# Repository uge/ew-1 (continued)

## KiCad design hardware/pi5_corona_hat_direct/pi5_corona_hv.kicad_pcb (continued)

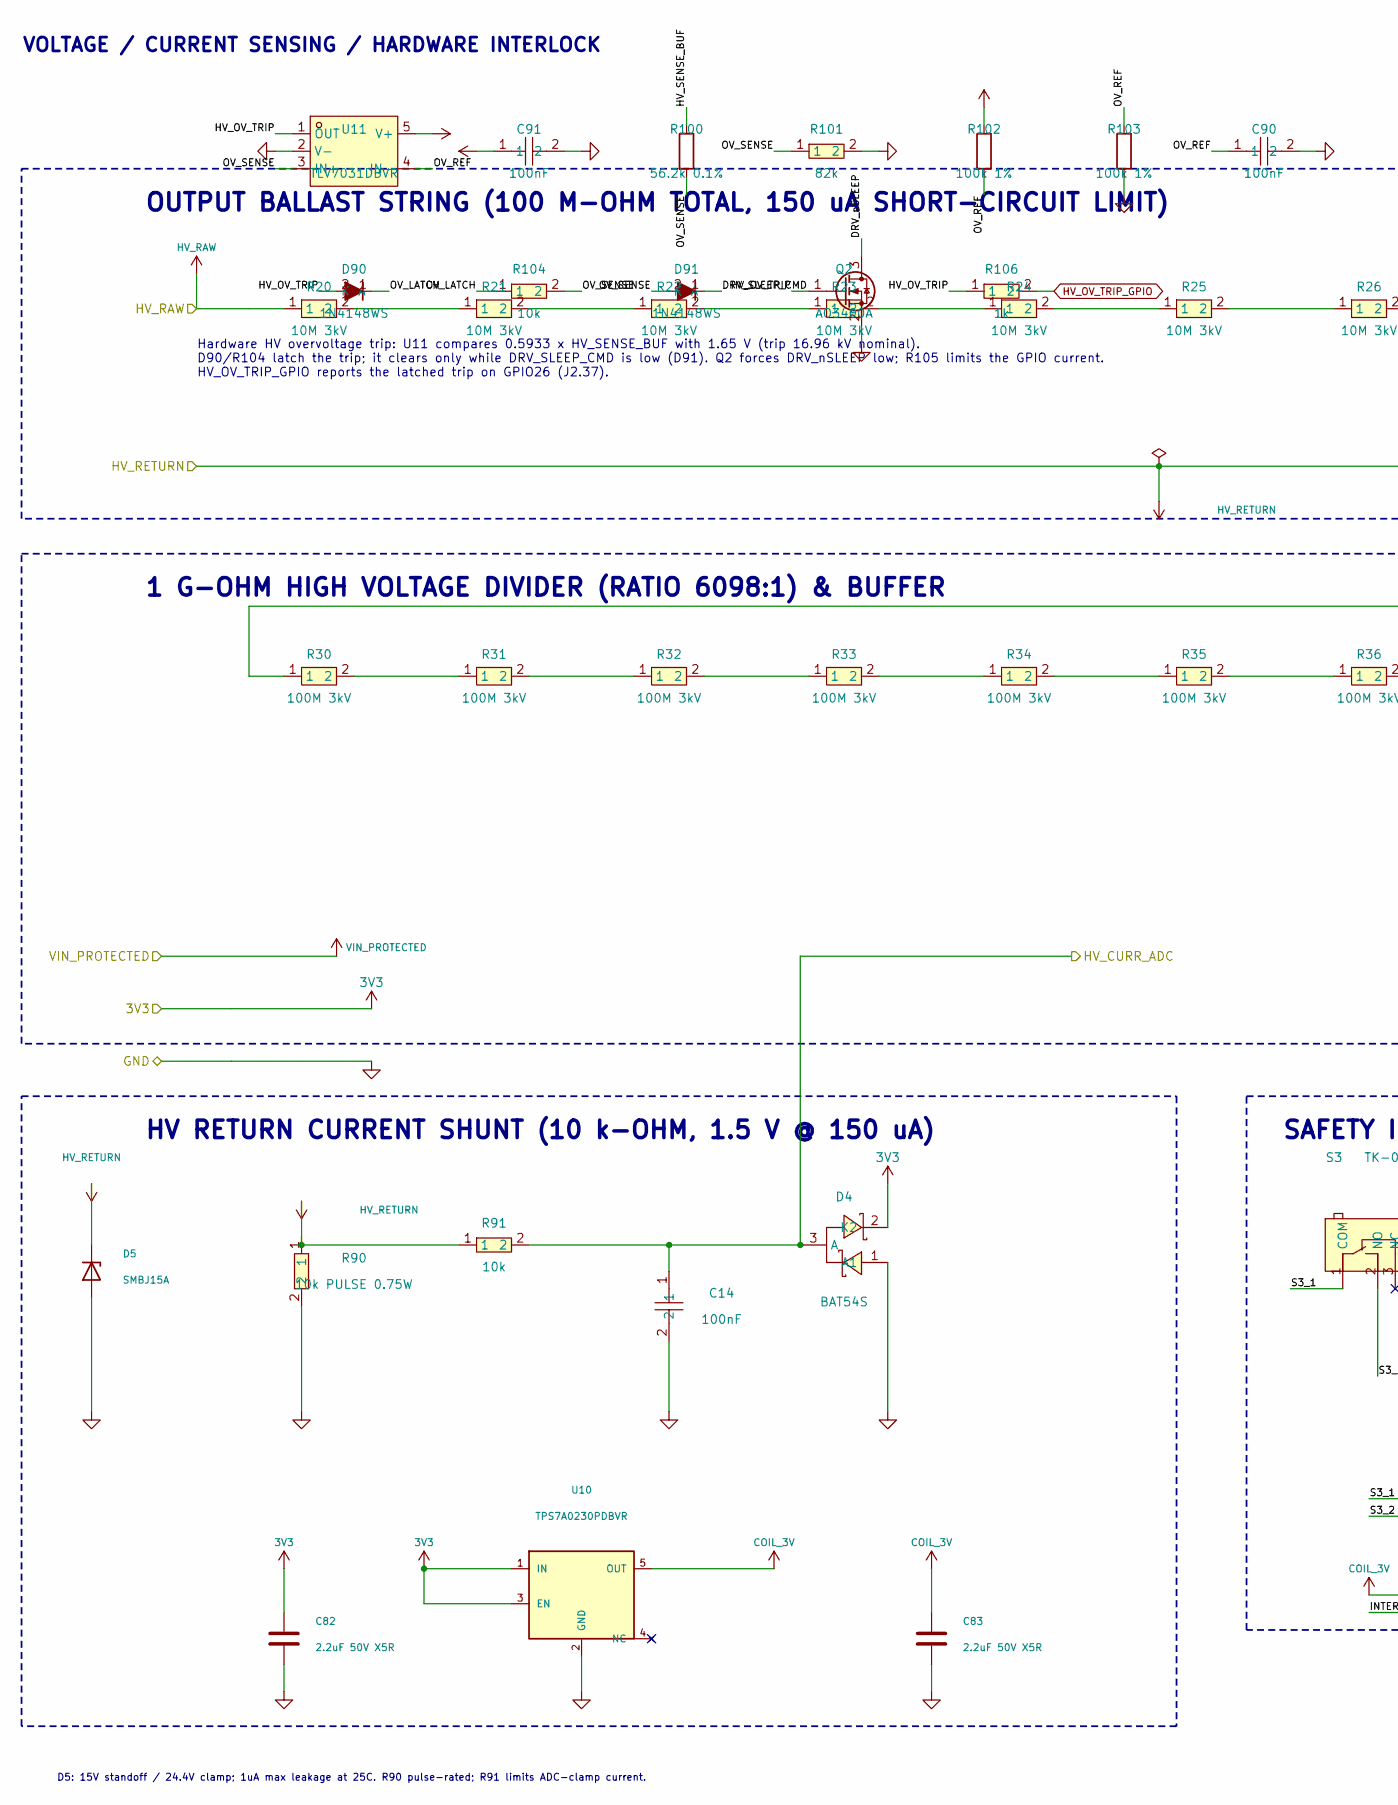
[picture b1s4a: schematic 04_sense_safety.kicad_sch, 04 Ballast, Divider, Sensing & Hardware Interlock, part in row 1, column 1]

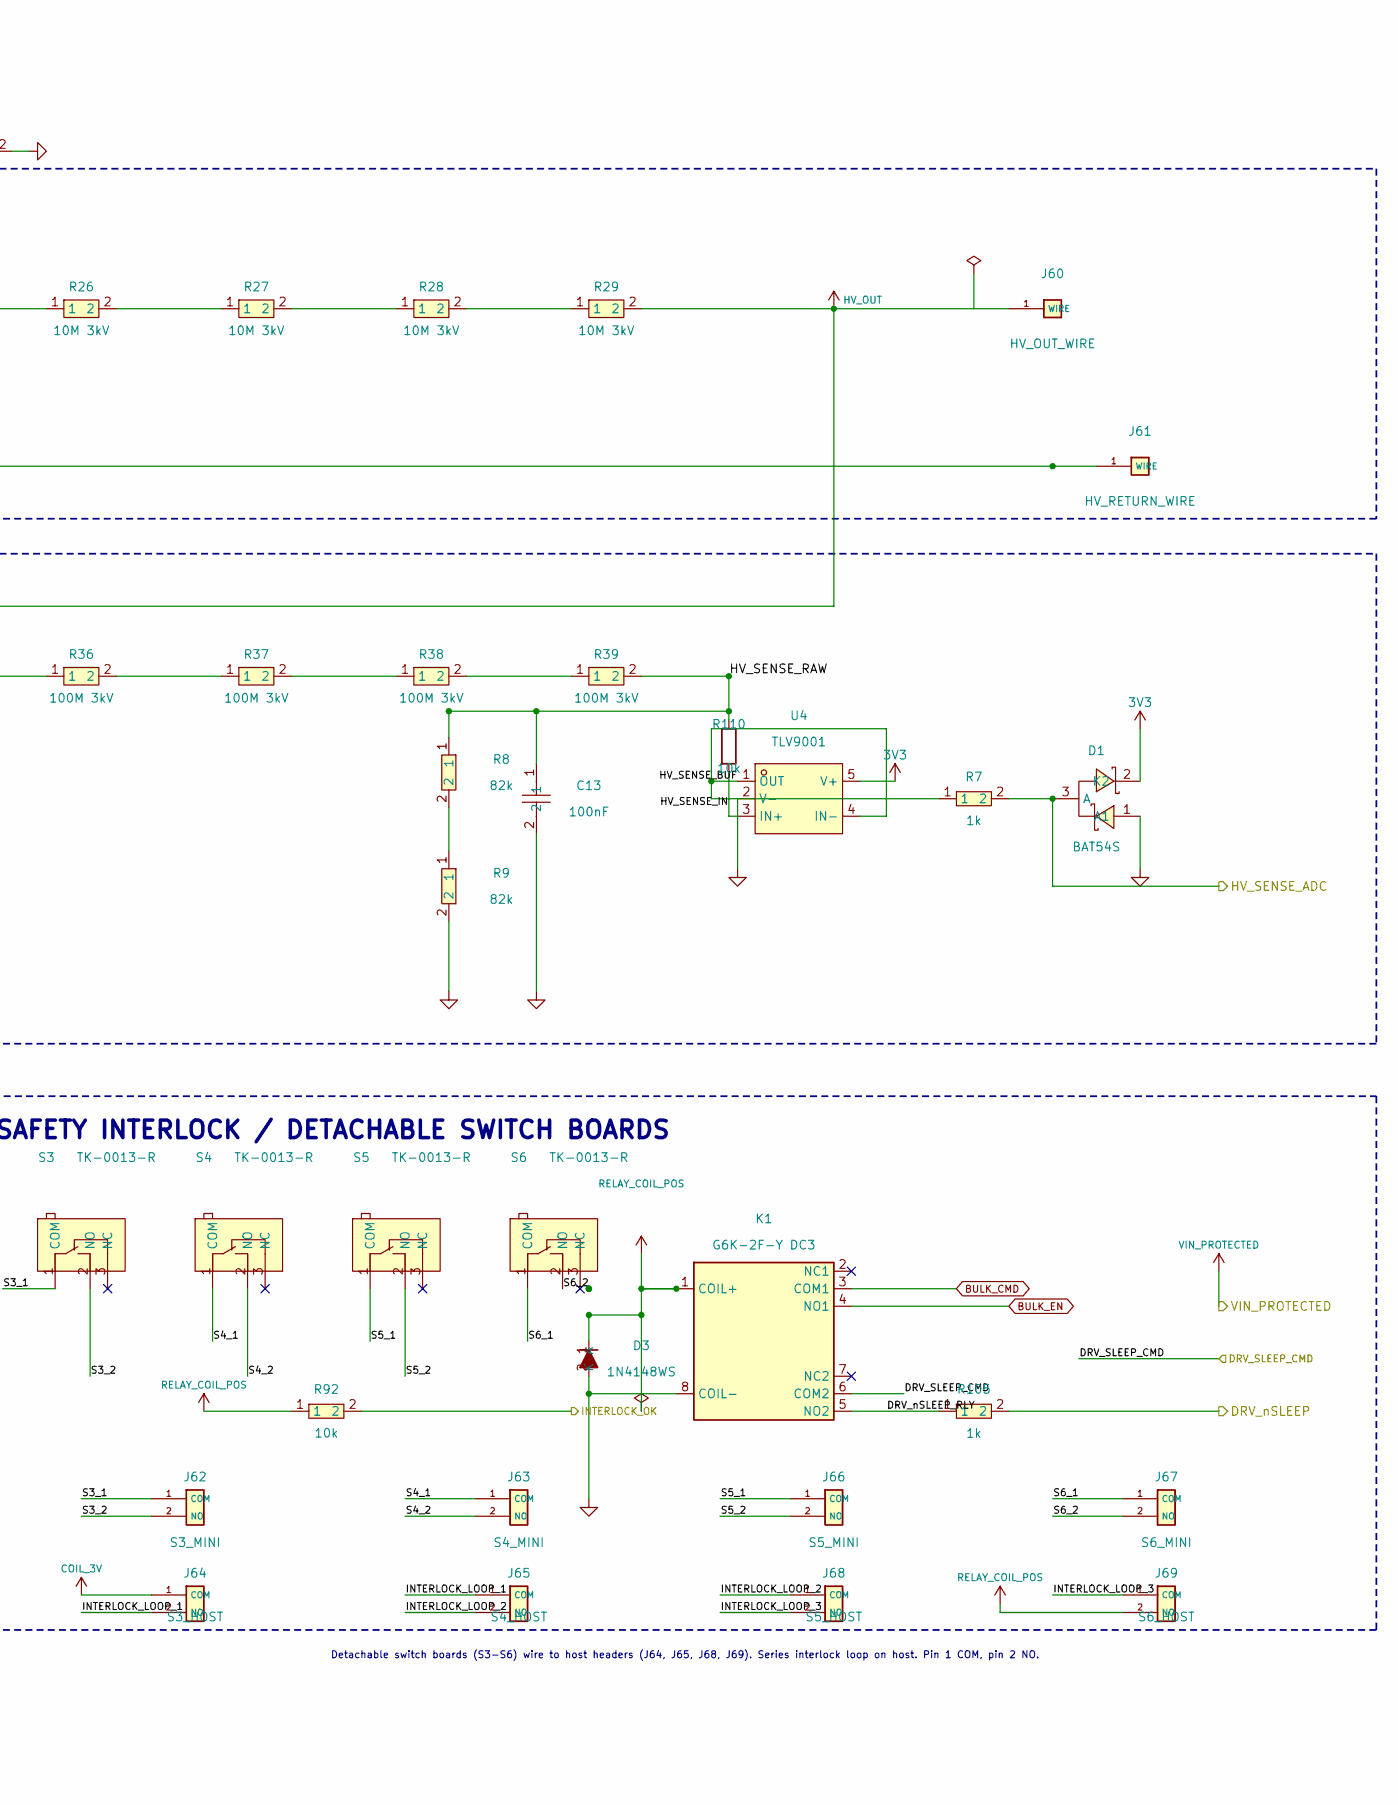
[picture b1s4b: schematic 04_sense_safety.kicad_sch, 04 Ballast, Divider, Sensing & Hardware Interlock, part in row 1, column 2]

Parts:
C13, C14, C90, C91: 100nF; C0603; MPN CC0603KRX7R9BB104; LCSC Part C14663
C82, C83: 2.2uF 50V X5R; C_0805_2012Metric; MPN CL21A225KBQNNNE; LCSC C377773
D1, D4: BAT54S; SOT-23-3_L2.9-W1.3-P1.90-LS2.4-BR; MPN BAT54S; LCSC Part C83935
D3, D90, D91: 1N4148WS; D_SOD-323; MPN 1N4148WS; LCSC Part C2128
D5: SMBJ15A; D_SMB; MPN SMBJ15A; LCSC C2912077
J60: HV_OUT_WIRE; HV_Wire_Termination_1P; JLCPCB Library PCB feature
J61: HV_RETURN_WIRE; HV_Wire_Termination_1P; JLCPCB Library PCB feature
J62: S3_MINI; Solder_Pads_2P_P5.08; JLCPCB Library PCB feature
J63: S4_MINI; Solder_Pads_2P_P5.08; JLCPCB Library PCB feature
J64: S3_HOST; Solder_Pads_2P_P5.08; JLCPCB Library PCB feature
J65: S4_HOST; Solder_Pads_2P_P5.08; JLCPCB Library PCB feature
J66: S5_MINI; Solder_Pads_2P_P5.08; JLCPCB Library PCB feature
J67: S6_MINI; Solder_Pads_2P_P5.08; JLCPCB Library PCB feature
J68: S5_HOST; Solder_Pads_2P_P5.08; JLCPCB Library PCB feature
J69: S6_HOST; Solder_Pads_2P_P5.08; JLCPCB Library PCB feature
K1: G6K-2F-Y DC3; Relay_DPDT_Omron_G6K-2F-Y; MPN G6K-2F-Y DC3; LCSC Part C93168
Q2: AO3400A; SOT-23; MPN AO3400A; LCSC Part C20917
R7, R105, R106: 1k; R0603; MPN 0603WAF1001T5E; LCSC Part C21190
R8, R9, R101: 82k; R0603; MPN 0603WAF8202T5E; LCSC Part C23254
R20, R21, R22, R23, R24, R25, R26, R27, R28, R29: 10M 3kV; R_2512_6332Metric; MPN CHV2512-JW-106ELF; LCSC Part C2095568
R30, R31, R32, R33, R34, R35, R36, R37, R38, R39: 100M 3kV; R_2512_6332Metric; MPN CHV2512-JW-107ELF; LCSC Part C2089706
R90: 10k PULSE 0.75W; R_1206_3216Metric; MPN CRCW120610K0FKEAHP; LCSC Part C313977
R91, R92, R104: 10k; R0603; MPN 0603WAF1002T5E; LCSC Part C25804
R100: 56.2k 0.1%; R_0603_1608Metric; MPN RT0603BRD0756K2L; LCSC Part C705784
R102, R103: 100k 1%; R_0603_1608Metric; MPN 0603WAF1003T5E; LCSC Part C25803
R110: 10k; R_0603_1608Metric; MPN 0603WAF1002T5E; LCSC Part C25804
S3, S4, S5, S6: TK-0013-R; SW_TK-0013-R; MPN TK-0013-R; LCSC Part C19724218
U4: TLV9001; SOT-23-5_L3.0-W1.7-P0.95-LS2.8-BR; MPN TLV9001IDBVR; LCSC Part C398363
U10: TPS7A0230PDBVR; SOT-23-5; MPN TPS7A0230PDBVR; LCSC C3747031
U11: TLV7031DBVR; SOT-23-5_L3.0-W1.7-P0.95-LS2.8-BR; MPN TLV7031DBVR; LCSC Part C2869832

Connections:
3V3: C82.1, C91.1, D1.2 (K2), D4.2 (K2), R102.1, U4.5 (V+), U10.1 (IN), U10.3 (EN), U11.5 (V+); also elsewhere on the board
/04_sense_safety/DRV_nSLEEP_RLY: K1.5 (NO2), R105.1
/04_sense_safety/HV_OUT: J60.1, R29.2, R30.1
/04_sense_safety/HV_OV_TRIP: D90.2 (A), Q2.1 (G), R106.1, U11.1 (OUT)
/04_sense_safety/HV_SENSE_BUF: R7.1, R100.1, U4.1 (OUT), U4.4 (IN-)
/04_sense_safety/HV_SENSE_IN: R110.2, U4.3 (IN+)
/04_sense_safety/HV_SENSE_RAW: C13.1, R8.1, R39.2, R110.1
/04_sense_safety/INTERLOCK_LOOP_1: J64.2 (NO), J65.1 (COM)
/04_sense_safety/INTERLOCK_LOOP_2: J65.2 (NO), J68.1 (COM)
/04_sense_safety/INTERLOCK_LOOP_3: J68.2 (NO), J69.1 (COM)
/04_sense_safety/OV_LATCH: D90.1 (K), R104.1
/04_sense_safety/OV_REF: C90.1, R102.2, R103.1, U11.4 (IN-)
/04_sense_safety/OV_SENSE: D91.2 (A), R100.2, R101.1, R104.2, U11.3 (IN+)
/04_sense_safety/RELAY_COIL_POS: D3.1 (K), J69.2 (NO), K1.1 (COIL+), R92.1
/04_sense_safety/S3_1: J62.1 (COM), S3.1 (COM)
/04_sense_safety/S3_2: J62.2 (NO), S3.2 (NO)
/04_sense_safety/S4_1: J63.1 (COM), S4.1 (COM)
/04_sense_safety/S4_2: J63.2 (NO), S4.2 (NO)
/04_sense_safety/S5_1: J66.1 (COM), S5.1 (COM)
/04_sense_safety/S5_2: J66.2 (NO), S5.2 (NO)
/04_sense_safety/S6_1: J67.1 (COM), S6.1 (COM)
/04_sense_safety/S6_2: J67.2 (NO), S6.2 (NO)
/DRV_SLEEP_CMD: D91.1 (K), K1.6 (COM2); also elsewhere on the board
/DRV_nSLEEP: Q2.3 (D), R105.2; also elsewhere on the board
/HV_CURR_ADC: C14.1, D4.3 (A), R91.2; also elsewhere on the board
/HV_RAW: R20.1; also elsewhere on the board
/HV_RETURN: D5.1 (K), J61.1, R90.1, R91.1
/HV_SENSE_ADC: D1.3 (A), R7.2; also elsewhere on the board
/INTERLOCK_OK: R92.2; also elsewhere on the board
BULK_CMD: K1.3 (COM1); also elsewhere on the board
BULK_EN: K1.4 (NO1); also elsewhere on the board
COIL_3V: C83.1, J64.1 (COM), U10.5 (OUT)
GND: C13.2, C14.2, C82.2, C83.2, C90.2, C91.2, D1.1 (A1), D3.2 (A), D4.1 (A1), D5.2 (A), K1.8 (COIL-), Q2.2 (S), R9.2, R90.2, R101.2, R103.2, U4.2 (V-), U10.2 (GND), U11.2 (V-); also elsewhere on the board
HV_OV_TRIP_GPIO: R106.2; also elsewhere on the board
unnamed: R8.2, R9.1
unnamed: R20.2, R21.1
unnamed: R21.2, R22.1
unnamed: R22.2, R23.1
unnamed: R23.2, R24.1
unnamed: R24.2, R25.1
unnamed: R25.2, R26.1
unnamed: R26.2, R27.1
unnamed: R27.2, R28.1
unnamed: R28.2, R29.1
unnamed: R30.2, R31.1
unnamed: R31.2, R32.1
unnamed: R32.2, R33.1
unnamed: R33.2, R34.1
unnamed: R34.2, R35.1
unnamed: R35.2, R36.1
unnamed: R36.2, R37.1
unnamed: R37.2, R38.1
unnamed: R38.2, R39.1

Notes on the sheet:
VOLTAGE / CURRENT SENSING / HARDWARE INTERLOCK
HV RETURN CURRENT SHUNT (10 k-OHM, 1.5 V @ 150 uA)
1 G-OHM HIGH VOLTAGE DIVIDER (RATIO 6098:1) & BUFFER
Detachable switch boards (S3-S6) wire to host headers (J64, J65, J68, J69). Series interlock loop on host. Pin 1 COM, pin 2 NO.
SAFETY INTERLOCK / DETACHABLE SWITCH BOARDS
D5: 15V standoff / 24.4V clamp; 1uA max leakage at 25C. R90 pulse-rated; R91 limits ADC-clamp current.
OUTPUT BALLAST STRING (100 M-OHM TOTAL, 150 uA SHORT-CIRCUIT LIMIT)
Hardware HV overvoltage trip: U11 compares 0.5933 x HV_SENSE_BUF with 1.65 V (trip 16.96 kV nominal). D90/R104 latch the trip; it clears only while DRV_SLEEP_CMD is low (D91). Q2 forces DRV_nSLEEP low; R105 limits the GPIO current. HV_OV_TRIP_GPIO reports the latched trip on GPIO26 (J2.37).

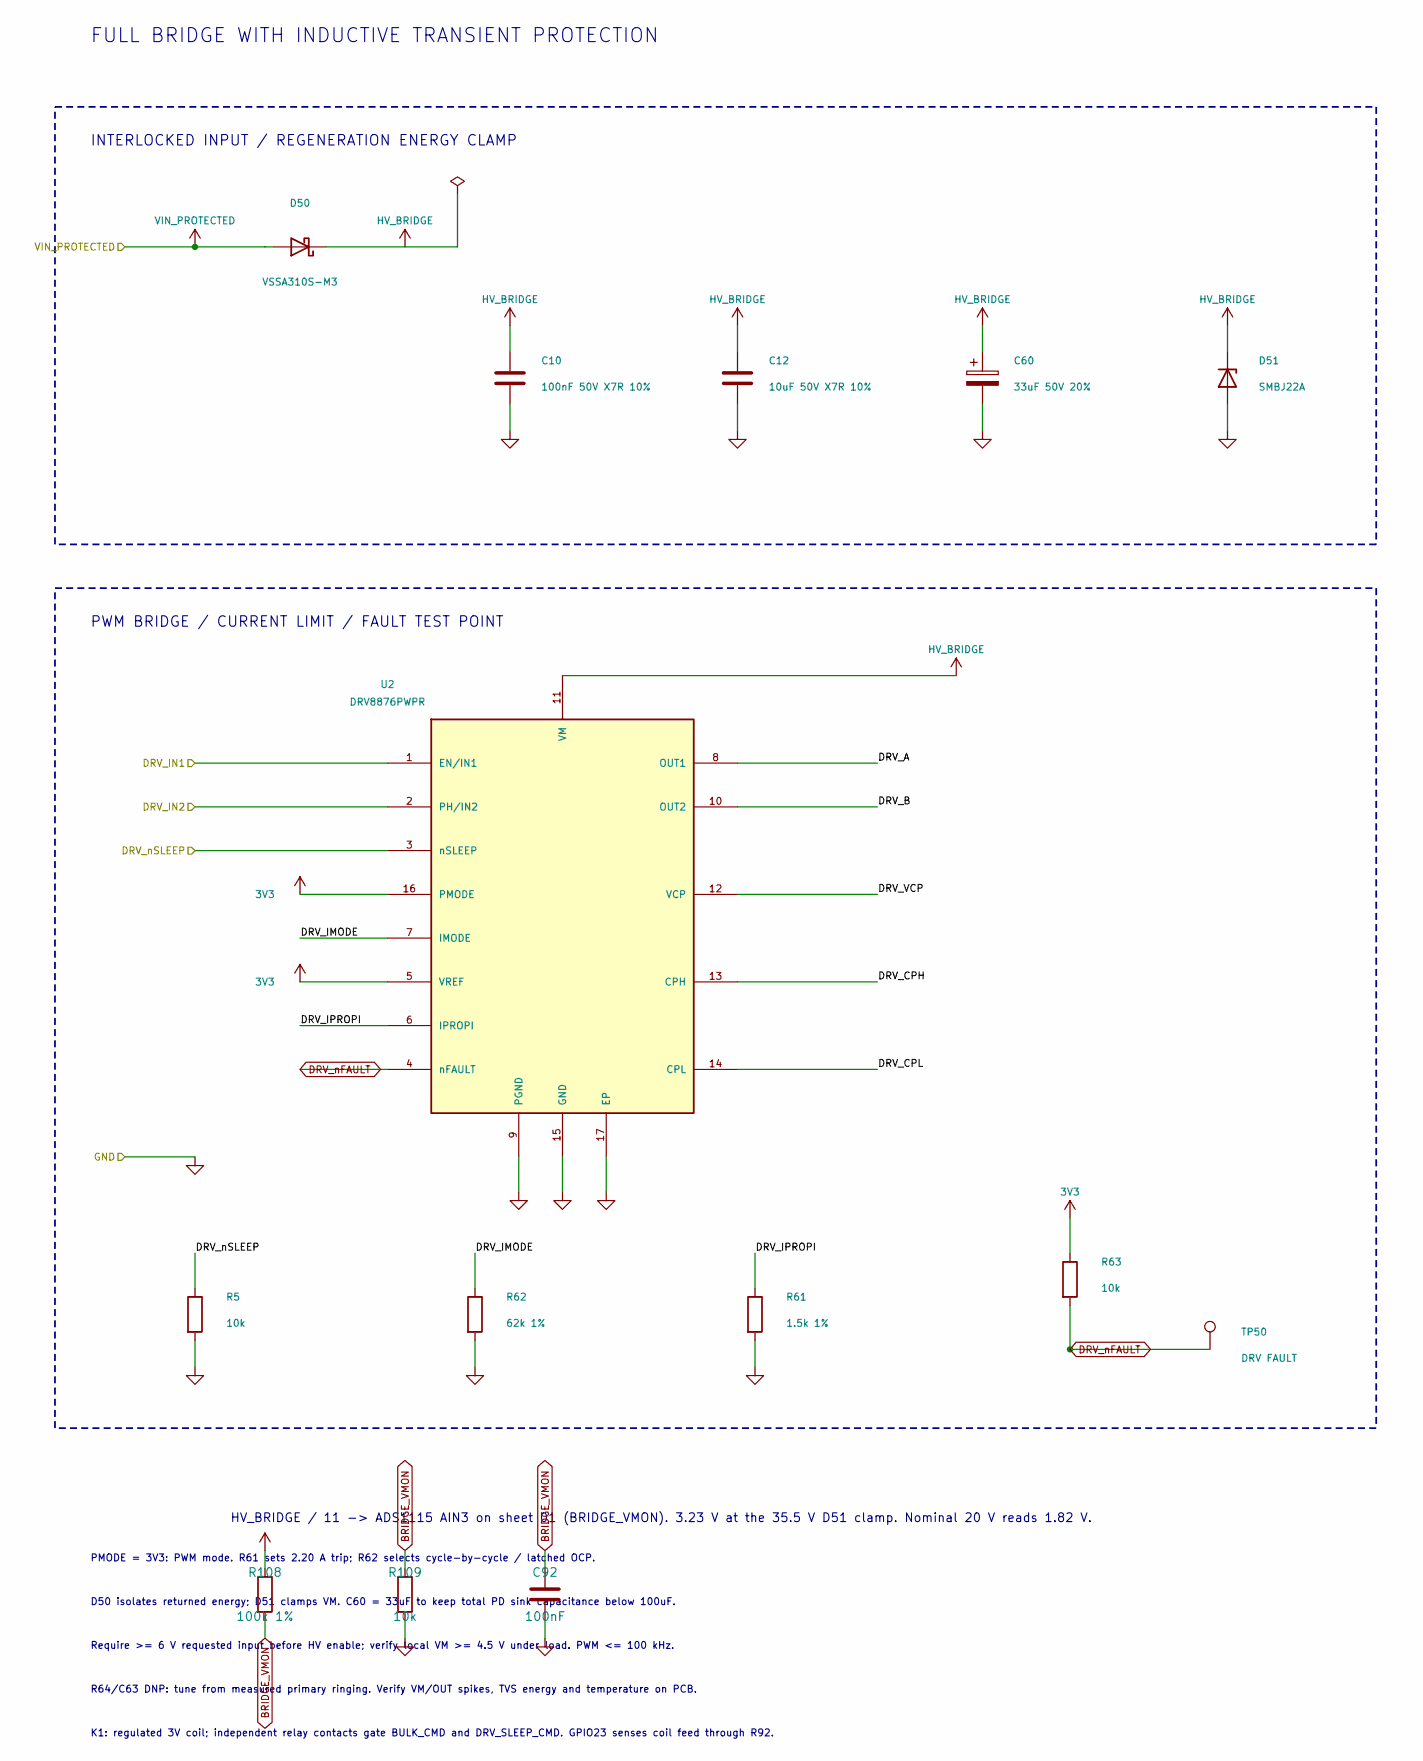
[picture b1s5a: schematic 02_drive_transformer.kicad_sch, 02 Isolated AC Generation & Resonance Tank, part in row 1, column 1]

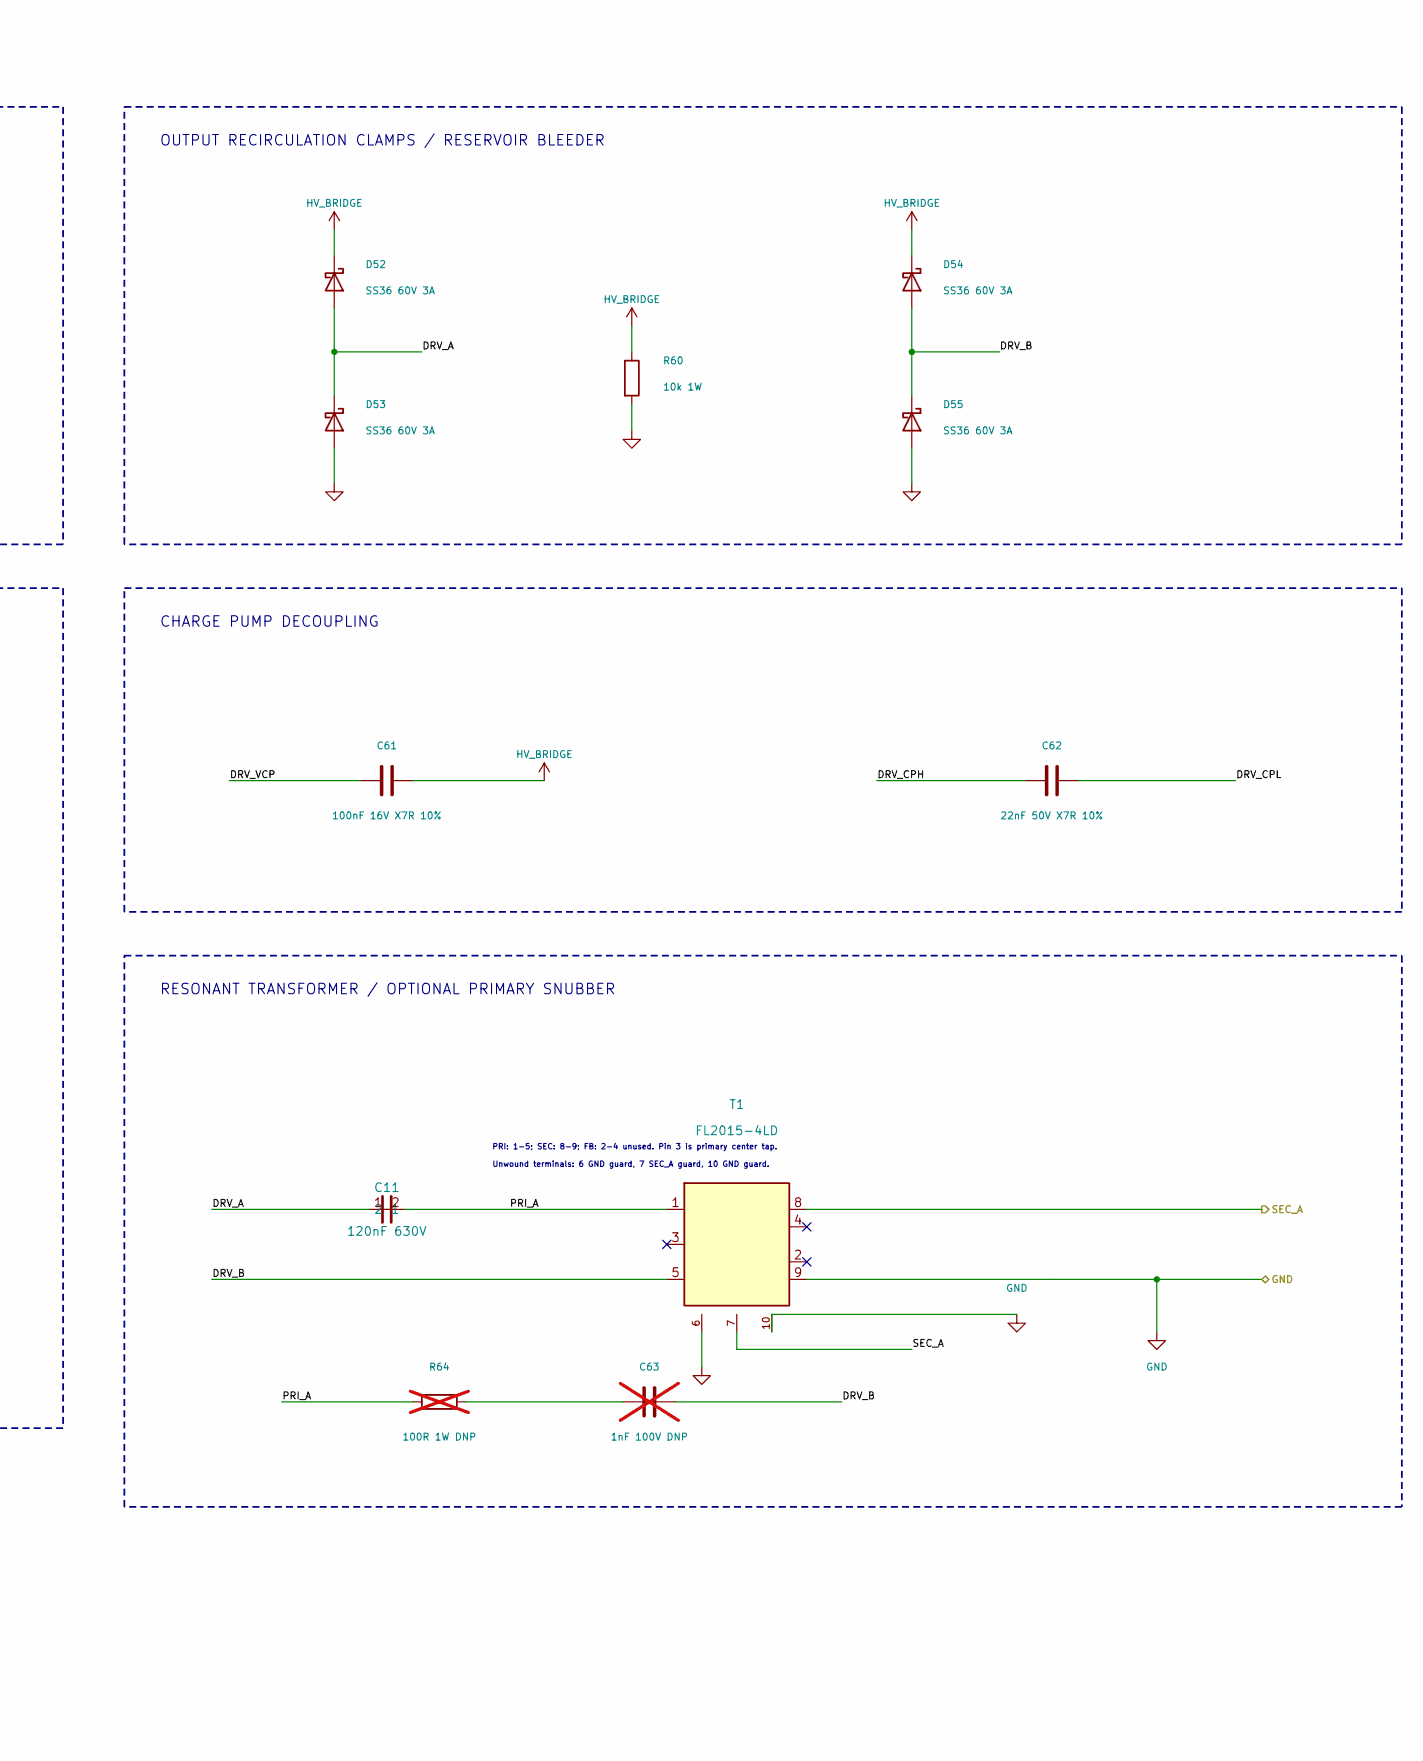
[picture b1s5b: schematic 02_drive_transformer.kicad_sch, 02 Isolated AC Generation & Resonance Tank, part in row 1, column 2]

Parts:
C10: 100nF 50V X7R 10%; C_0603_1608Metric; MPN CC0603KRX7R9BB104; LCSC C14663
C11: 120nF 630V; Film_KYET_18x10mm_P15mm; MPN MMKP124J2J1501; LCSC Part C2991056
C12: 10uF 50V X7R 10%; C_1210_3225Metric; MPN UMK325AB7106KMHP; LCSC C386166
C60: 33uF 50V 20%; CP_Radial_D5.0mm_P2.00mm; MPN 50YXJ33M5X11; LCSC C2839476
C61: 100nF 16V X7R 10%; C_0603_1608Metric; MPN CC0603KRX7R9BB104; LCSC C14663
C62: 22nF 50V X7R 10%; C_0603_1608Metric; MPN CL10B223KB8NNNC; LCSC C21122
C63: 1nF 100V DNP; C_0805_2012Metric; MPN GRM2165C2A102JA01D; LCSC C162289; not fitted
C92: 100nF; C_0603_1608Metric; MPN CC0603KRX7R9BB104; LCSC Part C14663
D50: VSSA310S-M3; D_SMA; MPN VSSA310S-M3/61T; LCSC C145232
D51: SMBJ22A; D_SMB; MPN SMBJ22A; LCSC C49066946
D52, D53, D54, D55: SS36 60V 3A; D_SMC; MPN SS36C; LCSC C16237
R5, R63: 10k; R_0603_1608Metric; MPN 0603WAF1002T5E; LCSC C25804
R60: 10k 1W; R_2512_6332Metric; MPN 25121WF1002T4E; LCSC C270956
R61: 1.5k 1%; R_0603_1608Metric; MPN 0603WAF1501T5E; LCSC C22843
R62: 62k 1%; R_0603_1608Metric; MPN 0603WAF6202T5E; LCSC C23221
R64: 100R 1W DNP; R_2512_6332Metric; MPN 25121WF1000T4E; LCSC C35218; not fitted
R108: 100k 1%; R_0603_1608Metric; MPN 0603WAF1003T5E; LCSC Part C25803
R109: 10k; R_0603_1608Metric; MPN 0603WAF1002T5E; LCSC Part C25804
T1: FL2015-4LD; Coilcraft_FL2015_Package1_SMT; MPN FL2015-4LD; JLCPCB Library Unknown
TP50: DRV FAULT; TestPoint_Pad_D1.5mm; JLCPCB Library Unknown
U2: DRV8876PWPR; HTSSOP-16-1EP_4.4x5mm_P0.65mm_EP3.4x5mm_Mask3x3mm_ThermalVi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; MPN DRV8876PWPR; LCSC C575551

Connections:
3V3: R63.1, U2.5 (VREF), U2.16 (PMODE); also elsewhere on the board
/02_drive_transformer/DRV_A: C11.1, D52.2 (A), D53.1 (K), U2.8 (OUT1)
/02_drive_transformer/DRV_B: C63.2, D54.2 (A), D55.1 (K), T1.5 (PRI_B), U2.10 (OUT2)
/02_drive_transformer/DRV_CPH: C62.1, U2.13 (CPH)
/02_drive_transformer/DRV_CPL: C62.2, U2.14 (CPL)
/02_drive_transformer/DRV_IMODE: R62.1, U2.7 (IMODE)
/02_drive_transformer/DRV_IPROPI: R61.1, U2.6 (IPROPI)
/02_drive_transformer/DRV_VCP: C61.1, U2.12 (VCP)
/02_drive_transformer/HV_BRIDGE: C10.1, C12.1, C60.1, C61.2, D50.1 (K), D51.1 (K), D52.1 (K), D54.1 (K), R60.1, R108.1, U2.11 (VM)
/02_drive_transformer/PRI_A: C11.2, R64.1, T1.1 (PRI_A)
/DRV_IN1: U2.1 (EN/IN1); also elsewhere on the board
/DRV_IN2: U2.2 (PH/IN2); also elsewhere on the board
/DRV_nSLEEP: R5.1, U2.3 (nSLEEP); also elsewhere on the board
/SEC_A: T1.7 (UNUSED_GUARD), T1.8 (SEC_A); also elsewhere on the board
/VIN_PROTECTED: D50.2 (A); also elsewhere on the board
BRIDGE_VMON: C92.1, R108.2, R109.1; also elsewhere on the board
DRV_nFAULT: R63.2, TP50.1, U2.4 (nFAULT); also elsewhere on the board
GND: C10.2, C12.2, C60.2, C92.2, D51.2 (A), D53.2 (A), D55.2 (A), R5.2, R60.2, R61.2, R62.2, R109.2, T1.6 (UNUSED_GUARD), T1.9 (SEC_B), T1.10 (UNUSED_GUARD), U2.9 (PGND), U2.15 (GND), U2.17 (EP); also elsewhere on the board
unnamed: C63.1, R64.2

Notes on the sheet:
INTERLOCKED INPUT / REGENERATION ENERGY CLAMP
Require >= 6 V requested input before HV enable; verify local VM >= 4.5 V under load. PWM <= 100 kHz.
FULL BRIDGE WITH INDUCTIVE TRANSIENT PROTECTION
PRI: 1-5; SEC: 8-9; FB: 2-4 unused. Pin 3 is primary center tap.
CHARGE PUMP DECOUPLING
RESONANT TRANSFORMER / OPTIONAL PRIMARY SNUBBER
Unwound terminals: 6 GND guard, 7 SEC_A guard, 10 GND guard.
D50 isolates returned energy; D51 clamps VM. C60 = 33uF to keep total PD sink capacitance below 100uF.
K1: regulated 3V coil; independent relay contacts gate BULK_CMD and DRV_SLEEP_CMD. GPIO23 senses coil feed through R92.
PMODE = 3V3: PWM mode. R61 sets 2.20 A trip; R62 selects cycle-by-cycle / latched OCP.
R64/C63 DNP: tune from measured primary ringing. Verify VM/OUT spikes, TVS energy and temperature on PCB.
OUTPUT RECIRCULATION CLAMPS / RESERVOIR BLEEDER
PWM BRIDGE / CURRENT LIMIT / FAULT TEST POINT
HV_BRIDGE / 11 -> ADS1115 AIN3 on sheet 01 (BRIDGE_VMON). 3.23 V at the 35.5 V D51 clamp. Nominal 20 V reads 1.82 V.

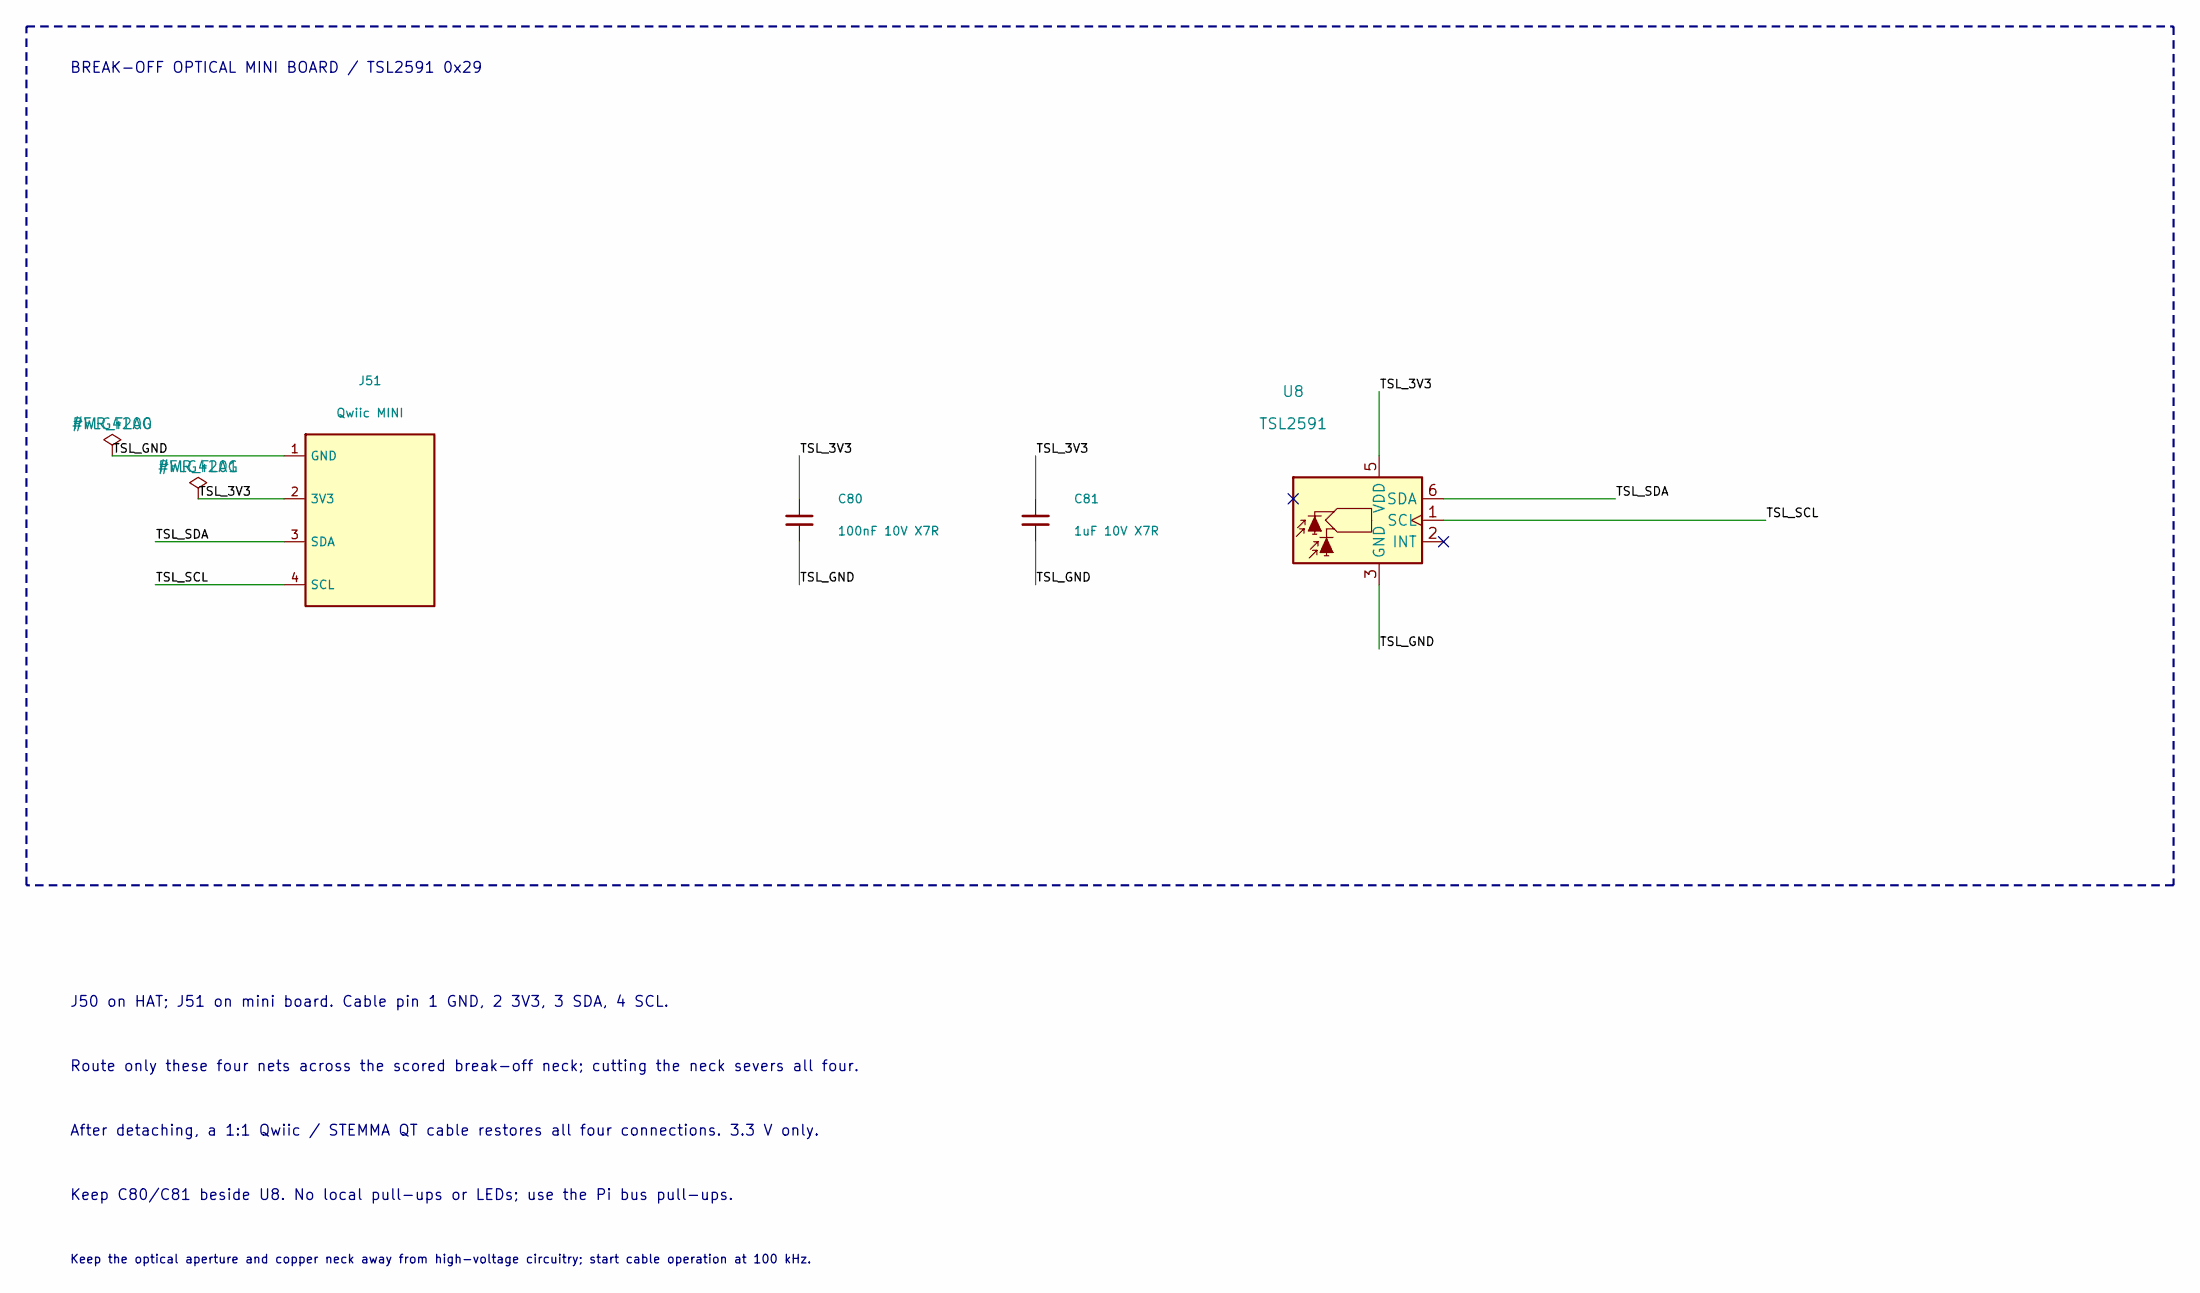
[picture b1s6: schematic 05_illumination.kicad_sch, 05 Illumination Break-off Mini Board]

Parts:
C80: 100nF 10V X7R; C_0603_1608Metric; MPN CC0603KRX7R9BB104; LCSC C14663
C81: 1uF 10V X7R; C_0603_1608Metric; MPN CL10B105KB8NQNC; LCSC C5199872
J51: Qwiic MINI; JST_SH_SM04B-SRSS-TB_1x04-1MP_P1.00mm_Horizontal; MPN SM04B-SRSS-TB(LF)(SN); LCSC C160404
U8: TSL2591; AMS_TSL25911FN; MPN TSL25911FN; LCSC C176812

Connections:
/05_illumination/TSL_3V3: C80.1, C81.1, J51.2 (3V3), U8.5 (VDD)
/05_illumination/TSL_GND: C80.2, C81.2, J51.1 (GND), U8.3 (GND)
/05_illumination/TSL_SCL: J51.4 (SCL), U8.1 (SCL)
/05_illumination/TSL_SDA: J51.3 (SDA), U8.6 (SDA)

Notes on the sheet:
BREAK-OFF OPTICAL MINI BOARD / TSL2591 0x29
Keep C80/C81 beside U8. No local pull-ups or LEDs; use the Pi bus pull-ups.
J50 on HAT; J51 on mini board. Cable pin 1 GND, 2 3V3, 3 SDA, 4 SCL.
Keep the optical aperture and copper neck away from high-voltage circuitry; start cable operation at 100 kHz.
After detaching, a 1:1 Qwiic / STEMMA QT cable restores all four connections. 3.3 V only.
Route only these four nets across the scored break-off neck; cutting the neck severs all four.

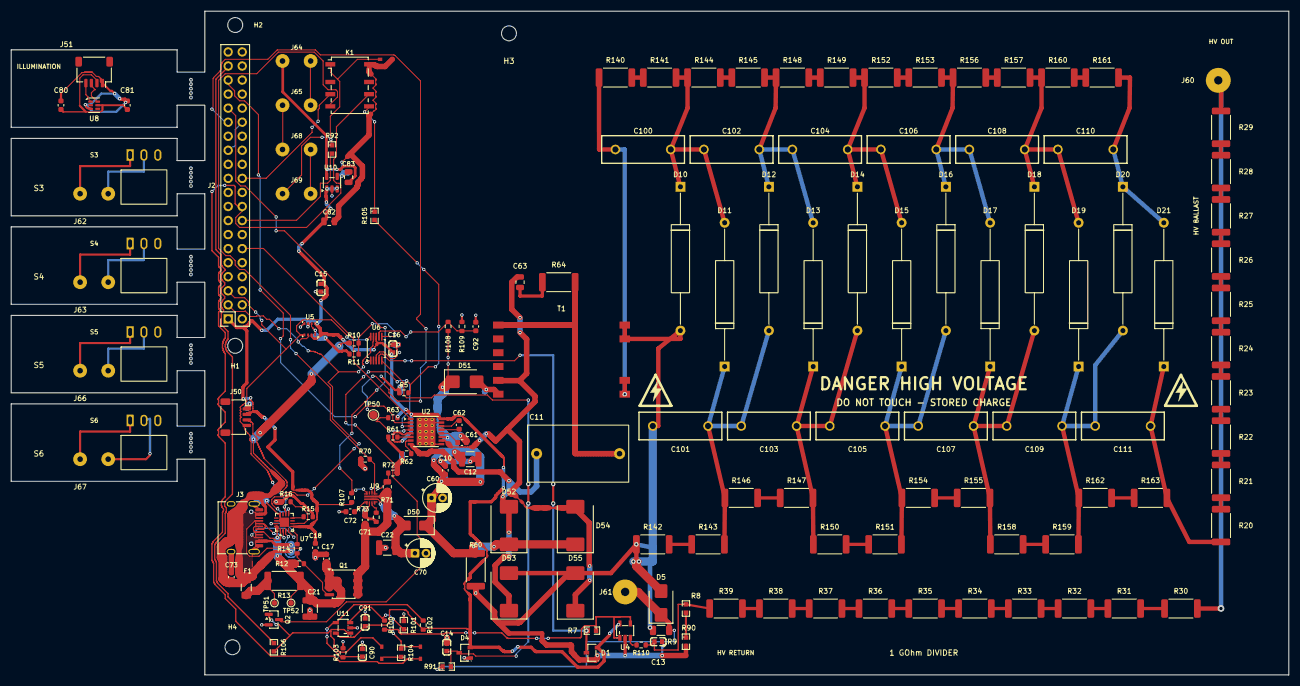
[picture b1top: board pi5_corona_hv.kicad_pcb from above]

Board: 2 copper layers, 231.0 x 120.0 mm, 185 parts (0 on the bottom side), 115 nets.

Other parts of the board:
H1, H2, H3, H4: MountingHole_2.7mm_M2.5
MB1, MB2, MB3, MB4, MB5: Mousebite_5x0.5mm_P0.8mm
MP1: Raspberry Pi 5 — DNP MECHANICAL; Raspberry_Pi_5_Mechanical

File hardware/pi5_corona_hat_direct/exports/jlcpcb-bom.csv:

Comment,Designator,Footprint,LCSC Part #
4.7uF 50V 10%,C21,Capacitor_SMD:C_1210_3225Metric,C126618
VSSA310S-M3,D50,Diode_SMD:D_SMA,C145232
100nF,"C10,C13,C14,C15,C16,C61,C71,C80",ionic_thrust_hv:C0603,C14663
1uF 16V 10%,C18,Capacitor_SMD:C_0603_1608Metric,C15849
2.2nF 50V 10%,C72,Capacitor_SMD:C_0603_1608Metric,C1604
SM04B-SRSS-TB(LF)(SN),"J50,J51",Connector_JST:JST_SH_SM04B-SRSS-TB_1x04-1MP_P1.00mm_Horizontal,C160404
AO4407A,Q1,Package_SO:SO-8_3.9x4.9mm_P1.27mm,C16072
SS36 60V 3A,"D52,D53,D54,D55",Diode_SMD:D_SMC,C16237
USB-C PD INPUT,J3,ionic_thrust_hv:USB_C_Receptacle_HRO_TYPE-C-31-M-12,C165948
TSL2591,U8,OptoDevice:AMS_TSL25911FN,C176812
TK-0013-R,"S3,S4,S5,S6",ionic_thrust_hv:SW_TK-0013-R,C19724218
100M 3kV,"R30,R31,R32,R33,R34,R35,R36,R37,R38,R39,R140,R141,R142,R143,R144,R145,R146,R147,R148,R149,R150,R151,R152,R153,R154,R155,R156,R157,R158,R159,R160,R161,R162,R163",Resistor_SMD:R_2512_6332Metric,C2089706
22nF 50V X7R 10%,C62,Capacitor_SMD:C_0603_1608Metric,C21122
1k,R7,ionic_thrust_hv:R0603,C21190
1N4148WS,D3,ionic_thrust_hv:D_SOD-323,C2128
SMBJ22A,D51,Diode_SMD:D_SMB,C224015
1.2k 1%,R73,Resistor_SMD:R_0603_1608Metric,C22765
1.5k 1%,R61,Resistor_SMD:R_0603_1608Metric,C22843
1M 1%,"R15,R16",Resistor_SMD:R_0603_1608Metric,C22935
62k 1%,R62,Resistor_SMD:R_0603_1608Metric,C23221
82k,"R8,R9",ionic_thrust_hv:R0603,C23254
HUSB238A-BB001-QN16R,U7,ionic_thrust_hv:QFN-16-1EP_3x3mm_P0.5mm_EP1.7x1.7mm,C24833806
100k 1%,"R10,R12,R70",Resistor_SMD:R_0603_1608Metric,C25803
10k,"R5,R63,R91,R92",Resistor_SMD:R_0603_1608Metric,C25804
18k 1%,R11,Resistor_SMD:R_0603_1608Metric,C25810
47k 1%,R14,Resistor_SMD:R_0603_1608Metric,C25816
33uF 50V 20%,C60,Capacitor_THT:CP_Radial_D5.0mm_P2.00mm,C2839476
SMBJ15A,D5,Diode_SMD:D_SMB,C2912077
Pi 5 HAT 2x20,J2,Connector_PinSocket_2.54mm:PinSocket_2x20_P2.54mm_Vertical,C2977589
120nF 630V,C11,ionic_thrust_hv:Film_KYET_18x10mm_P15mm,C2991056
10k PULSE 0.75W,R90,Resistor_SMD:R_1206_3216Metric,C313977
TPS259470LRPW,U9,ionic_thrust_hv:Texas_RPW0010A_VQFN-HR-10_2x2mm,C3662793
TPS7A0230PDBVR,U10,Package_TO_SOT_SMD:SOT-23-5,C3747031
ADS1115,U6,Package_SO:TSSOP-10_3x3mm_P0.5mm,C37593
2.2uF 50V X5R,"C82,C83",Capacitor_SMD:C_0805_2012Metric,C377773
10uF 50V 10%,"C12,C22",Capacitor_SMD:C_1210_3225Metric,C386166
5mR 1%,R13,Resistor_SMD:R_2512_6332Metric,C393074
TLV9001,U4,ionic_thrust_hv:SOT-23-5_L3.0-W1.7-P0.95-LS2.8-BR,C398363
2A 24V PTC,F1,Fuse:Fuse_1206_3216Metric,C42396578
2CL75,"D10,D11,D12,D13,D14,D15,D16,D17,D18,D19,D20,D21",ionic_thrust_hv:Sunmate_2CL75_D3_L12_P26,C424512
1uF 50V 10%,"C17,C73,C81",Capacitor_SMD:C_0603_1608Metric,C5199872
1k 1W,R60,Resistor_SMD:R_2512_6332Metric,C54315
DRV8876PWPR,U2,Package_SO:HTSSOP-16-1EP_4.4x5mm_P0.65mm_EP3.4x5mm_Mask3x3mm_ThermalVias,C575551
56.2k 0.1%,R72,Resistor_SMD:R_0603_1608Metric,C705784
BAT54S,"D1,D4",ionic_thrust_hv:SOT-23-3_L2.9-W1.3-P1.90-LS2.4-BR,C83935
976k 0.1%,R71,Resistor_SMD:R_0805_2012Metric,C865713
22uF 50V 20%,C70,Capacitor_THT:CP_Radial_D5.0mm_P2.00mm,C88755
BME280,U5,Package_LGA:Bosch_LGA-8_2.5x2.5mm_P0.65mm_ClockwisePinNumbering,C92489
G6K-2F-Y DC3,K1,Relay_SMD:Relay_DPDT_Omron_G6K-2F-Y,C93168
